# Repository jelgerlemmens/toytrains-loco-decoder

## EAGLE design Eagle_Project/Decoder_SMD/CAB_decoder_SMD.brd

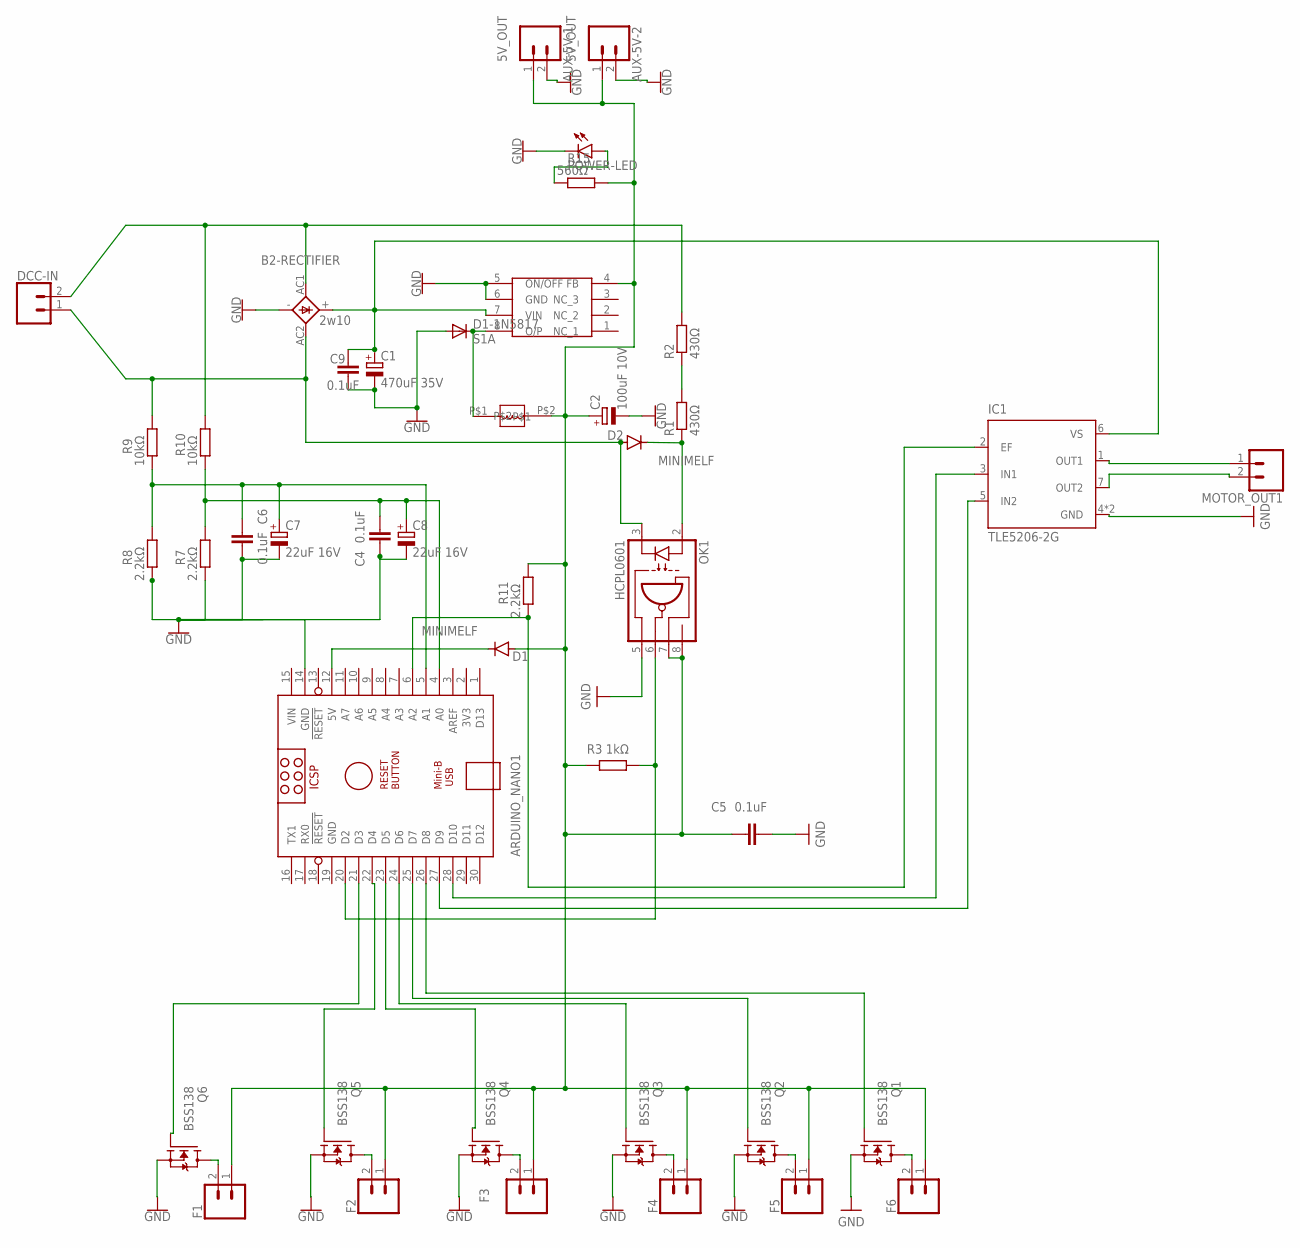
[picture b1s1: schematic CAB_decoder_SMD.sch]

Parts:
ARDUINO_NANO1: ARDUINO_NANO
AUX-5V-1, AUX-5V-2: 5V_OUT; MOLEX-1X2_LOCK
B2-RECTIFIER: 2w10; 1KAB
C1: 470uF 35V; 153CLV-1014
C2: 100uF 10V; 153CLV-0605
C4, C5, C6, C9: 0.1uF; C1206
C7, C8: 22uF 16V; 153CLV-0405
D1, D2: MINIMELF
D1-1N5817: S1A; DO214AC
DCC-IN: CONN_02POLAR_LOCK; MOLEX-1X2_LOCK
F1, F2, F3, F4, F5, F6: CONN_02POLAR_LOCK; MOLEX-1X2_LOCK
IC1: TLE5206-2G; P-TO263-7-1
MOTOR_OUT1: CONN_02POLAR_LOCK; MOLEX-1X2_LOCK
OK1: HCPL0601; SOIC08
POWER-LED: LEDCHIPLED_1206; CHIPLED_1206
Q1, Q2, Q3, Q4, Q5, Q6: BSS138; SOT23
R1, R2: 430Ω; R2512
R3: 1kΩ; R1206
R7, R8, R11: 2.2kΩ; R1206
R9, R10: 10kΩ; R1206
R15: 560Ω; R1206
U$1: LM2594; SOIC8
U$2: L-CD54; L_CD54

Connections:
5V: AUX-5V-1.1, AUX-5V-2.1, C2.+, C5.1, D1.A, F1.1, F2.1, F3.1, F4.1, F5.1, F6.1, OK1.7 (VE), OK1.8 (VCC), R3.2, R11.1, R15.1, U$1.4 (FB), U$2.P$2
20V: B2-RECTIFIER.+, C1.+, C9.1, IC1.6 (VS), U$1.7 (VIN)
GND: ARDUINO_NANO1.14 (GND), ARDUINO_NANO1.19 (GND), AUX-5V-1.2, AUX-5V-2.2, B2-RECTIFIER.-, C1.-, C2.-, C4.1, C5.2, C6.2, C7.-, C8.-, C9.2, D1-1N5817.A, IC1.4 (GND), IC1.8 (GND), OK1.5 (GND), POWER-LED.C, Q1.2 (S), Q2.2 (S), Q3.2 (S), Q4.2 (S), Q5.2 (S), Q6.2 (S), R7.2, R8.2, U$1.5 (ON/OFF), U$1.6 (GND)
HV-DCC-SIG-ONE: B2-RECTIFIER.AC2, D2.A, DCC-IN.1, OK1.3 (C), R9.1
HV-DCC-SIG-TWO: B2-RECTIFIER.AC1, DCC-IN.2, R2.2, R10.1
unnamed: D1-1N5817.C, U$1.8 (O/P), U$2.P$1
unnamed: ARDUINO_NANO1.22 (D4), Q5.1 (G)
unnamed: D2.C, OK1.2 (A), R1.1
unnamed: ARDUINO_NANO1.6 (A2), IC1.2 (EF), R11.2
unnamed: R1.2, R2.1
unnamed: IC1.7 (OUT2), MOTOR_OUT1.2
unnamed: ARDUINO_NANO1.5 (A1), C6.1, C7.+, R8.1, R9.2
unnamed: ARDUINO_NANO1.28 (D10), IC1.3 (IN1)
unnamed: ARDUINO_NANO1.27 (D9), IC1.5 (IN2)
unnamed: ARDUINO_NANO1.21 (D3), Q6.1 (G)
unnamed: ARDUINO_NANO1.4 (A0), C4.2, C8.+, R7.1, R10.2
unnamed: ARDUINO_NANO1.23 (D5), Q4.1 (G)
unnamed: ARDUINO_NANO1.24 (D6), Q3.1 (G)
unnamed: ARDUINO_NANO1.25 (D7), Q2.1 (G)
unnamed: ARDUINO_NANO1.26 (D8), Q1.1 (G)
unnamed: F6.2, Q1.3 (D)
unnamed: F5.2, Q2.3 (D)
unnamed: F3.2, Q4.3 (D)
unnamed: ARDUINO_NANO1.20 (D2), OK1.6 (VO), R3.1
unnamed: IC1.1 (OUT1), MOTOR_OUT1.1
unnamed: POWER-LED.A, R15.2
unnamed: ARDUINO_NANO1.12 (5V), D1.C
unnamed: F4.2, Q3.3 (D)
unnamed: F2.2, Q5.3 (D)
unnamed: F1.2, Q6.3 (D)
VIN: ARDUINO_NANO1.15 (VIN)

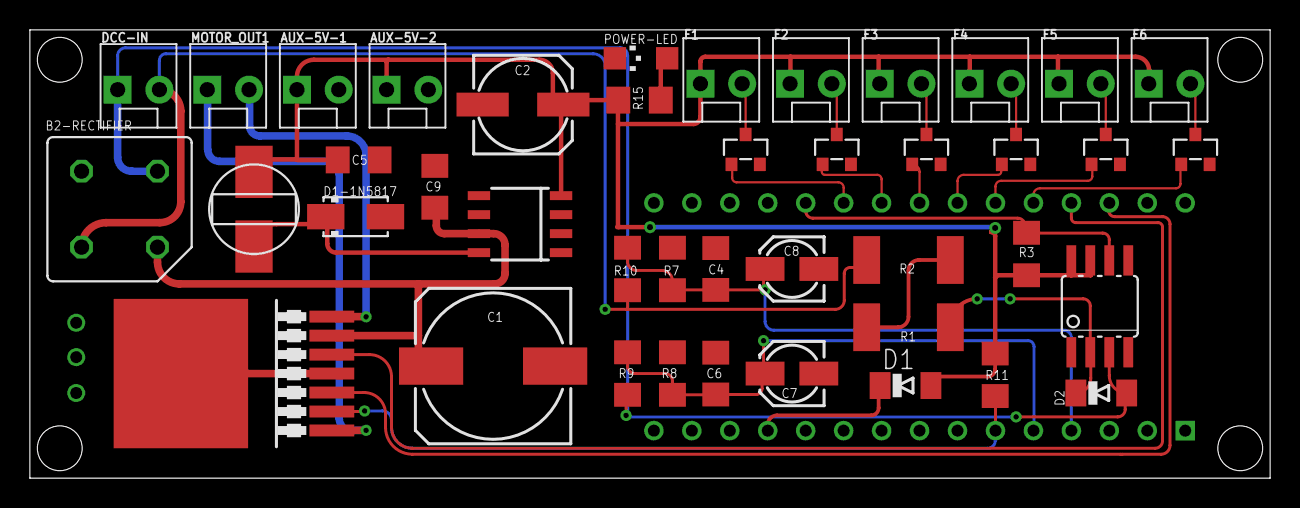
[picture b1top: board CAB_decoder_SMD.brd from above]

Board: 2 copper layers, 83.0 x 30.0 mm, 43 parts (1 on the bottom side), 30 nets.

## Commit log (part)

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2020-10-27 test commit
2020-11-20 H-bridge: TLE5206-G SMD
2020-11-20 H-bridge: TLE5206-G SMD 2
2021-02-11 Included AutoDesk Eagle designs
2026-04-24 esp32_decoder kicad setup
2026-04-24 gitignore updated
2026-04-24 pincontroller updated

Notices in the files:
parts and their libraries:
SparkFun-Connectors: Licensing: Creative Commons ShareAlike 4.0 International - https://creativecommons.org/licenses/by-sa/4.0
